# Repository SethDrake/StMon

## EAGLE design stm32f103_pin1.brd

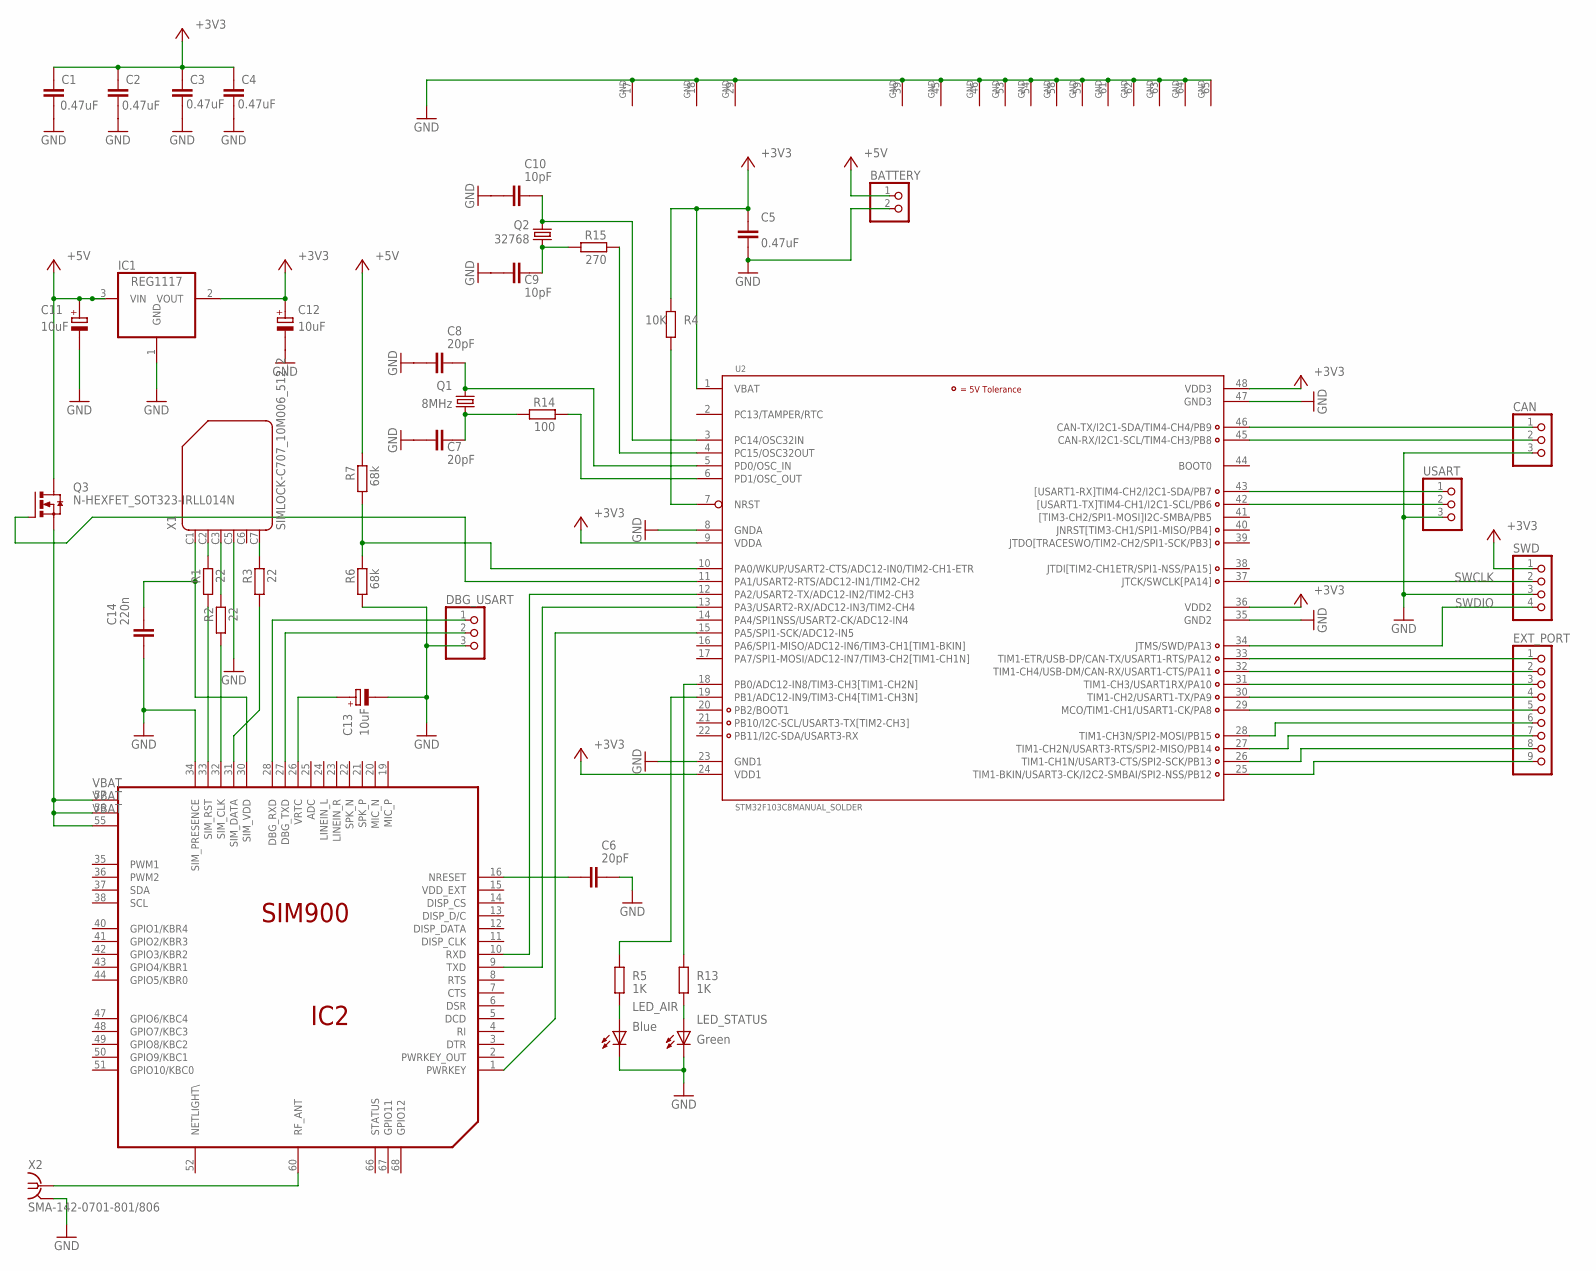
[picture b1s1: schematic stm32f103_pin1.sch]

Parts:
BATTERY: PINHD-1X2; 1X02
C1, C2, C3, C4, C5: 0.47uF; CAPC2012X145AN
C6, C7, C8: 20pF; CAPC2012X145AN
C9, C10: 10pF; CAPC2012X145AN
C11, C12, C13: 10uF; CAPMP3216X180N
C14: 220n; CAPC2012X145AN
CAN: PINHD-1X3; 1X03
DBG_USART: PINHD-1X3; 1X03
EXT_PORT: PINHD-1X9; 1X09
IC1: REG1117; SOT223
IC2: SIM900
LED_AIR: Blue; CHIP-LED0805
LED_STATUS: Green; CHIP-LED0805
Q1: 8MHz; HC49/S
Q2: 32768; TC38H
Q3: N-HEXFET_SOT323-IRLL014N; SOT223
R1, R2, R3: 22; RESC2012X70N
R4: 10K; RESC2012X70N
R5, R13: 1K; RESC2012X70N
R6, R7: 68k; RESC2012X70N
R14: 100; RESC2012X70N
R15: 270; RESC2012X70N
SWD: PINHD-1X4; 1X04
U2: STM32F103C8MANUAL_SOLDER; LQFP48_IGORL
USART: PINHD-1X3; 1X03
X1: SIMLOCK-C707_10M006_512_2; C707_10M006_512_2
X2: SMA-142-0701-801/806; J502-ND-142-0701-801/806

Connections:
+3V3: C1.1, C2.1, C3.1, C4.1, C5.1, C12.+, IC1.2 (VOUT), R4.2, SWD.1, U2.1 (VBAT), U2.9 (VDDA), U2.24 (VDD1), U2.36 (VDD2), U2.48 (VDD3)
+5V: BATTERY.1, C11.+, IC1.3 (VIN), Q3.4 (D), R7.1
GND: BATTERY.2, C1.2, C2.2, C3.2, C4.2, C5.2, C6.1, C7.2, C8.2, C9.2, C10.2, C11.-, C12.-, C13.-, C14.2, CAN.3, DBG_USART.3, IC1.1 (GND), IC2.17 (GND), IC2.18 (GND), IC2.29 (GND), IC2.34 (SIM_PRESENCE), IC2.39 (GND), IC2.45 (GND), IC2.46 (GND), IC2.53 (GND), IC2.54 (GND), IC2.58 (GND), IC2.59 (GND), IC2.61 (GND), IC2.62 (GND), IC2.63 (GND), IC2.64 (GND), IC2.65 (GND), LED_AIR.C, LED_STATUS.C, R6.2, SWD.3, U2.8 (GNDA), U2.23 (GND1), U2.35 (GND2), U2.47 (GND3), USART.3, X1.C5 (4), X2.G@1 (GND), X2.G@2 (GND), X2.G@3 (GND), X2.G@4 (GND)
unnamed: IC2.10 (RXD), U2.12 (PA2/USART2-TX/ADC12-IN2/TIM2-CH3)
unnamed: R15.1, U2.4 (PC15/OSC32OUT)
unnamed: C7.1, Q1.1, R14.2
unnamed: C10.1, Q2.2, U2.3 (PC14/OSC32IN)
unnamed: IC2.9 (TXD), U2.13 (PA3/USART2-RX/ADC12-IN3/TIM2-CH4)
unnamed: IC2.1 (PWRKEY), U2.15 (PA5/SPI1-SCK/ADC12-IN5)
unnamed: C9.1, Q2.1, R15.2
unnamed: IC2.60 (RF_ANT), X2.1
unnamed: C8.1, Q1.2, U2.5 (PD0/OSC_IN)
unnamed: R14.1, U2.6 (PD1/OSC_OUT)
unnamed: R4.1, U2.7 (NRST)
unnamed: C14.1, IC2.30 (SIM_VDD), X1.C1 (1)
unnamed: IC2.33 (SIM_RST), R1.2
unnamed: IC2.32 (SIM_CLK), R2.2
unnamed: IC2.31 (SIM_DATA), R3.2
unnamed: R3.1, X1.C7 (6)
unnamed: C6.2, IC2.16 (NRESET)
unnamed: R1.1, X1.C2 (2)
unnamed: R2.1, X1.C3 (3)
unnamed: DBG_USART.2, IC2.27 (DBG_TXD)
unnamed: DBG_USART.1, IC2.28 (DBG_RXD)
unnamed: C13.+, IC2.26 (VRTC)
unnamed: CAN.2, U2.45 (CAN-RX/I2C1-SCL/TIM4-CH3/PB8)
unnamed: U2.42 ([USART1-TX]TIM4-CH1/I2C1-SCL/PB6), USART.2
unnamed: U2.43 ([USART1-RX]TIM4-CH2/I2C1-SDA/PB7), USART.1
unnamed: EXT_PORT.1, U2.33 (TIM1-ETR/USB-DP/CAN-TX/USART1-RTS/PA12)
unnamed: EXT_PORT.2, U2.32 (TIM1-CH4/USB-DM/CAN-RX/USART1-CTS/PA11)
unnamed: EXT_PORT.3, U2.31 (TIM1-CH3/USART1RX/PA10)
unnamed: EXT_PORT.4, U2.30 (TIM1-CH2/USART1-TX/PA9)
unnamed: EXT_PORT.5, U2.29 (MCO/TIM1-CH1/USART1-CK/PA8)
unnamed: EXT_PORT.6, U2.28 (TIM1-CH3N/SPI2-MOSI/PB15)
unnamed: EXT_PORT.7, U2.27 (TIM1-CH2N/USART3-RTS/SPI2-MISO/PB14)
unnamed: EXT_PORT.8, U2.26 (TIM1-CH1N/USART3-CTS/SPI2-SCK/PB13)
unnamed: EXT_PORT.9, U2.25 (TIM1-BKIN/USART3-CK/I2C2-SMBAI/SPI2-NSS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)
unnamed: CAN.1, U2.46 (CAN-TX/I2C1-SDA/TIM4-CH4/PB9)
unnamed: R13.2, U2.18 (PB0/ADC12-IN8/TIM3-CH3[TIM1-CH2N])
unnamed: LED_STATUS.A, R13.1
unnamed: LED_AIR.A, R5.1
unnamed: R5.2, U2.19 (PB1/ADC12-IN9/TIM3-CH4[TIM1-CH3N])
unnamed: R6.1, R7.2, U2.10 (PA0/WKUP/USART2-CTS/ADC12-IN0/TIM2-CH1-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)
unnamed: Q3.1 (G), U2.11 (PA1/USART2-RTS/ADC12-IN1/TIM2-CH2)
unnamed: IC2.55 (VBAT), IC2.56 (VBAT), IC2.57 (VBAT), Q3.3 (S)
PA13: SWD.4, U2.34 (JTMS/SWD/PA13)
PA14: SWD.2, U2.37 (JTCK/SWCLK[PA14])

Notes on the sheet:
SWDIO
SWCLK

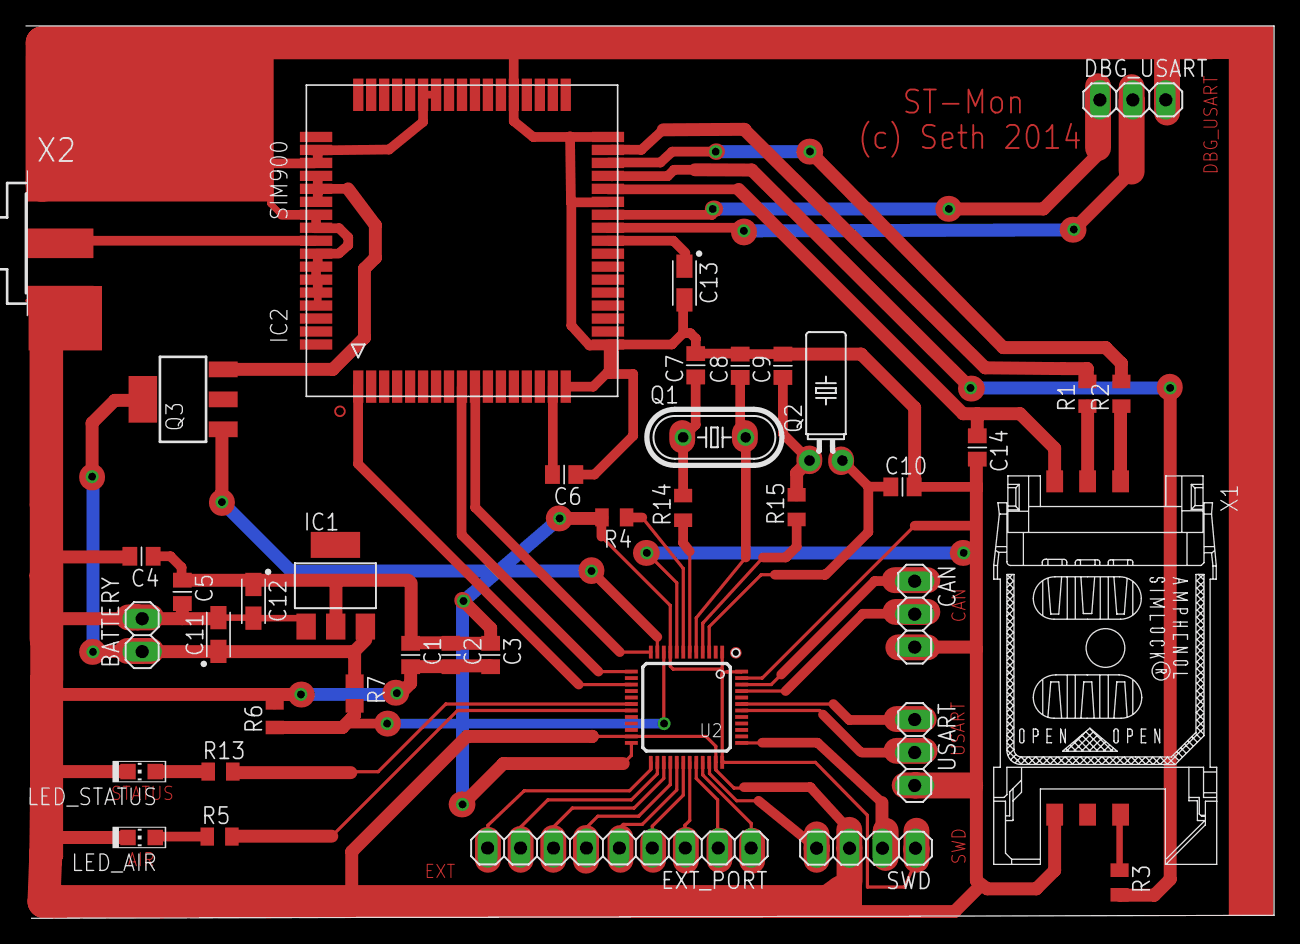
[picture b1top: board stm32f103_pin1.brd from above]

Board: 2 copper layers, 96.2 x 68.8 mm, 40 parts (0 on the bottom side), 47 nets.

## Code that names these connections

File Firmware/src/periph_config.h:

#pragma once
#ifndef __PERIPH_CONFIG_H_
#define __PERIPH_CONFIG_H_

/* PA13, PA14 - SWD - DON'T USE!!! */
/* PA11, PA12 - USB */

#define I2C_PORT		GPIOB
#define I2C_SCL			GPIO_PIN_6
#define I2C_SDA			GPIO_PIN_7

#define LEDS_PORT		GPIOB
#define LED_STAT_PIN	GPIO_PIN_0
#define LED_AIR_PIN		GPIO_PIN_1

#define USART_PORT		GPIOA
#define USART_TX	    GPIO_PIN_2
#define USART_RX		GPIO_PIN_3

#define BAT_CHECK_PORT	GPIOA
#define BAT_CHECK_PIN	GPIO_PIN_0

#define GSM_PWR_PORT	GPIOA
#define GSM_PWR_PIN		GPIO_PIN_1

#endif //__PERIPH_CONFIG_H_

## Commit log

2017-10-21 StMon src
2017-10-21 dev in progress..

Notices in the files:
parts and their libraries:
SparkFun-FreqCtrl: Licensing: CC v3.0 Share-Alike You are welcome to use this library for commercial purposes.
